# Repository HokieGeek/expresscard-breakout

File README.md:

# expresscard-breakout
Simple breakout board for an expresscard socket

## Schematic and board

# ExpressCard Pinouts

http://www.usb.org/developers/expresscard/EC_specifications/ExpressCard_2_0_FINAL.pdf

## Pin groups

### Power

 #  | Name | Function
--- | ---- | --------
 1  |  GND | Ground pin closest to the USB pins
 9  | 1.5v | Not sure what I would use these for, but nice to have access to them
10  | 1.5v | 
14  | 3.3v | Again, not sure if I should break out both of these...
15  | 3.3v | 
20  |  GND | These next three are closest to the PCI Express pins
23  |  GND |
26  |  GND |

I probably don't need to break out these individually. Probably need at most two GND, one 1.5v and one 3.3v

### USB

 #  | Name | Function
--- | ---- | -------- 
 2  | USB D- | USB Data line
 3  | USB D+ | USB Data line
 4  | CPUSB# | Indicate presence of USB module by wiring to GND

### PCI Express

 #  | Name | Function
--- | ---- | --------
 13 | PERST# | A reset?
 16 | CLKREQ# | Request that REFCLK be enabled
 17 | CPPE# | Indicates presence of PCI Express module by wiring to GND
 18 | REFCLK- | 
 19 | REFCLK+ |
 21 | PERn0 | Receive differential pair
 22 | PERp0 |
 24 | PETn0 | Transmit differential pair
 25 | PETp0 |
 
### SMBus

 #  | Name | Function
--- | ---- | --------
 7  | SMBDATA |
 8  | SMBCLK |

### Others

 #  | Name | Function
--- | ---- | --------
 11 | WAKE# | Turns the host on
 12 | 3.3v AUX | Voltage reference source for WAKE#

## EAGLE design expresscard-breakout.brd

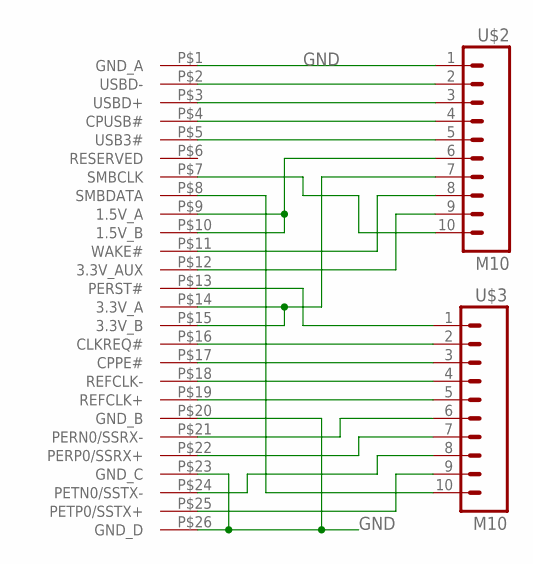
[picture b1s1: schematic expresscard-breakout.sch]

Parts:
U$1: EXPRESSCARD34
U$2, U$3: M10; 1X10-SMD-NOHOLES

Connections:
GND: U$1.P$1 (GND_A), U$1.P$20 (GND_B), U$1.P$23 (GND_C), U$1.P$26 (GND_D), U$2.1
unnamed: U$1.P$9 (1.5V_A), U$1.P$10 (1.5V_B), U$2.6
unnamed: U$1.P$2 (USBD-), U$2.2
unnamed: U$1.P$3 (USBD+), U$2.3
unnamed: U$1.P$4 (CPUSB#), U$2.4
unnamed: U$1.P$5 (USB3#), U$2.5
unnamed: U$1.P$14 (3.3V_A), U$1.P$15 (3.3V_B), U$2.7
unnamed: U$1.P$11 (WAKE#), U$2.8
unnamed: U$1.P$12 (3.3V_AUX), U$2.9
unnamed: U$1.P$7 (SMBCLK), U$2.10
unnamed: U$1.P$8 (SMBDATA), U$3.10
unnamed: U$1.P$13 (PERST#), U$3.1
unnamed: U$1.P$16 (CLKREQ#), U$3.2
unnamed: U$1.P$17 (CPPE#), U$3.3
unnamed: U$1.P$18 (REFCLK-), U$3.4
unnamed: U$1.P$19 (REFCLK+), U$3.5
unnamed: U$1.P$21 (PERN0/SSRX-), U$3.6
unnamed: U$1.P$22 (PERP0/SSRX+), U$3.7
unnamed: U$1.P$24 (PETN0/SSTX-), U$3.8
unnamed: U$1.P$25 (PETP0/SSTX+), U$3.9

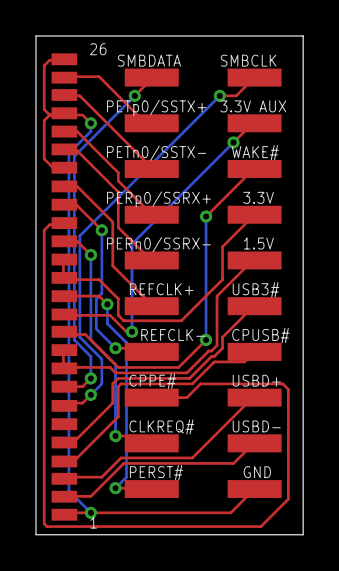
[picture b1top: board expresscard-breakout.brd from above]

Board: 2 copper layers, 14.8 x 27.7 mm, 3 parts (0 on the bottom side), 20 nets.

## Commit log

2015-11-05 Added some references and the list of pins of interest
2015-11-05 Added some commenting and SMBus
2015-11-05 Removed two
2015-11-05 Finally got the references in
2015-11-06 Initial layout with new device
2015-11-07 I think it is done
2015-11-07 *sigh*
2015-11-07 Cleaned up the image for the board
2018-01-08 Made the expresscard pads smaller (by 2mil) and brought them closer in to each other
